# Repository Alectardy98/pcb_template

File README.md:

# PCB Template 
    A template pcb made on www.keebal.com

All Supported Layouts can be seen [here](http://www.keyboard-layout-editor.com/#/gists/8a30e97cff93e199c105295b596f17f3)

USB/QMK atmega32u4 pcb for The RAMA x ION Zenith

- The firmware can be found in the firmware folder
- All files for production though JLCPCB can be found in the JLCPCB folder
- This PCB supports an ATMEGA32u4-AU and works via qmk
- Layouts support both MX and alps Switches

Released without warranty, use at your own risk.  

---
| Authors | 

Alectardy98

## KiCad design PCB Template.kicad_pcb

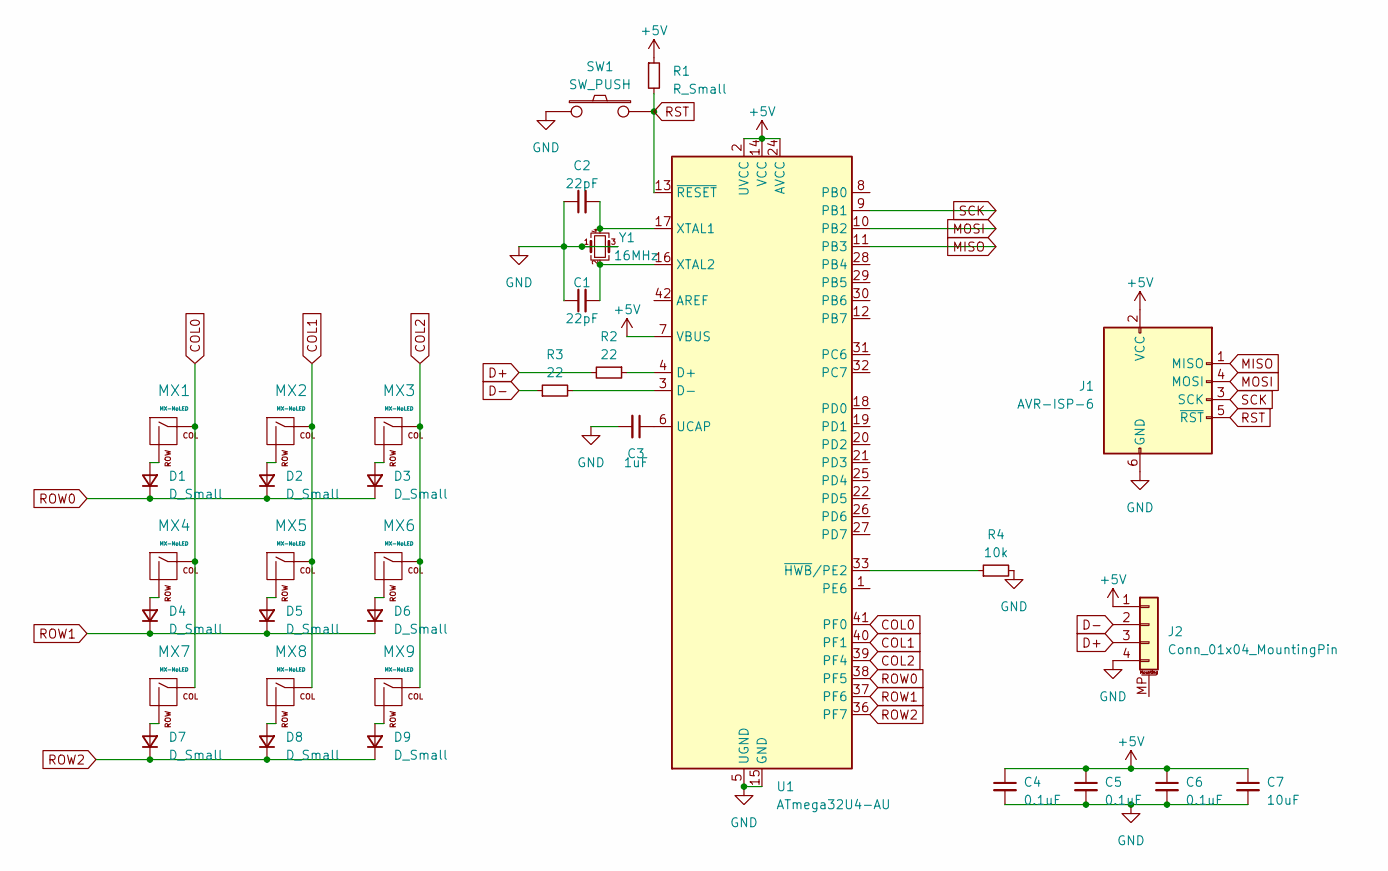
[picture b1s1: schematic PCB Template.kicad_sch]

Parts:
C1, C2: 22pF; C_0805_2012Metric
C3: 1uF; C_0805_2012Metric
C4, C5, C6: 0.1uF; C_0805_2012Metric
C7: 10uF; C_0805_2012Metric
D1, D2, D3, D4, D5, D6, D7, D8, D9: D_Small; D_SOD-123
J1: AVR-ISP-6; PinSocket_2x03_P2.54mm_Vertical
J2: Conn_01x04_MountingPin; JST_SH_SM04B-SRSS-TB_1x04-1MP_P1.00mm_Horizontal
MX1, MX2, MX3, MX4, MX5, MX6, MX7, MX8, MX9: MX-NoLED; MX-1U-NoLED
R1: R_Small
R2, R3: 22; R_0805_2012Metric
R4: 10k; R_0805_2012Metric
SW1: SW_PUSH
U1: ATmega32U4-AU; atmega32u4-mu-and-au
Y1: 16MHz; Crystal_SMD_3225-4Pin_3.2x2.5mm

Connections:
+5V: C4.1, C5.1, C6.1, C7.1, J1.2 (VCC), J2.1, R1.1, U1.2 (UVCC), U1.7 (VBUS), U1.14 (VCC), U1.24 (AVCC), U1.34 (VCC), U1.44 (AVCC)
COL0: MX1.1 (COL), MX4.1 (COL), MX7.1 (COL), U1.41 (PF0)
COL1: MX2.1 (COL), MX5.1 (COL), MX8.1 (COL), U1.40 (PF1)
COL2: MX3.1 (COL), MX6.1 (COL), MX9.1 (COL), U1.39 (PF4)
D+: J2.3, R2.2
D-: J2.2, R3.1
GND: C1.1, C2.1, C3.2, C4.2, C5.2, C6.2, C7.2, J1.6 (GND), J2.4, R4.2, SW1.1, U1.5 (UGND), U1.15 (GND), U1.23 (GND), U1.35 (GND), U1.43 (GND), U1.45, Y1.1, Y1.3
MISO: J1.1 (MISO), U1.11 (PB3)
MOSI: J1.4 (MOSI), U1.10 (PB2)
unnamed: D1.2 (A), MX1.2 (ROW)
unnamed: D2.2 (A), MX2.2 (ROW)
unnamed: D3.2 (A), MX3.2 (ROW)
unnamed: D4.2 (A), MX4.2 (ROW)
unnamed: D5.2 (A), MX5.2 (ROW)
unnamed: D6.2 (A), MX6.2 (ROW)
unnamed: D7.2 (A), MX7.2 (ROW)
unnamed: D8.2 (A), MX8.2 (ROW)
unnamed: D9.2 (A), MX9.2 (ROW)
unnamed: R2.1, U1.4 (D+)
unnamed: R3.2, U1.3 (D-)
unnamed: C3.1, U1.6 (UCAP)
unnamed: C2.2, U1.17 (XTAL1), Y1.4
unnamed: C1.2, U1.16 (XTAL2), Y1.2
unnamed: R4.1, U1.33 (~HWB/PE2)
ROW0: D1.1 (K), D2.1 (K), D3.1 (K), U1.38 (PF5)
ROW1: D4.1 (K), D5.1 (K), D6.1 (K), U1.37 (PF6)
ROW2: D7.1 (K), D8.1 (K), D9.1 (K), U1.36 (PF7)
RST: J1.5 (~RST), R1.2, SW1.2, U1.13 (~RESET)
SCK: J1.3 (SCK), U1.9 (PB1)

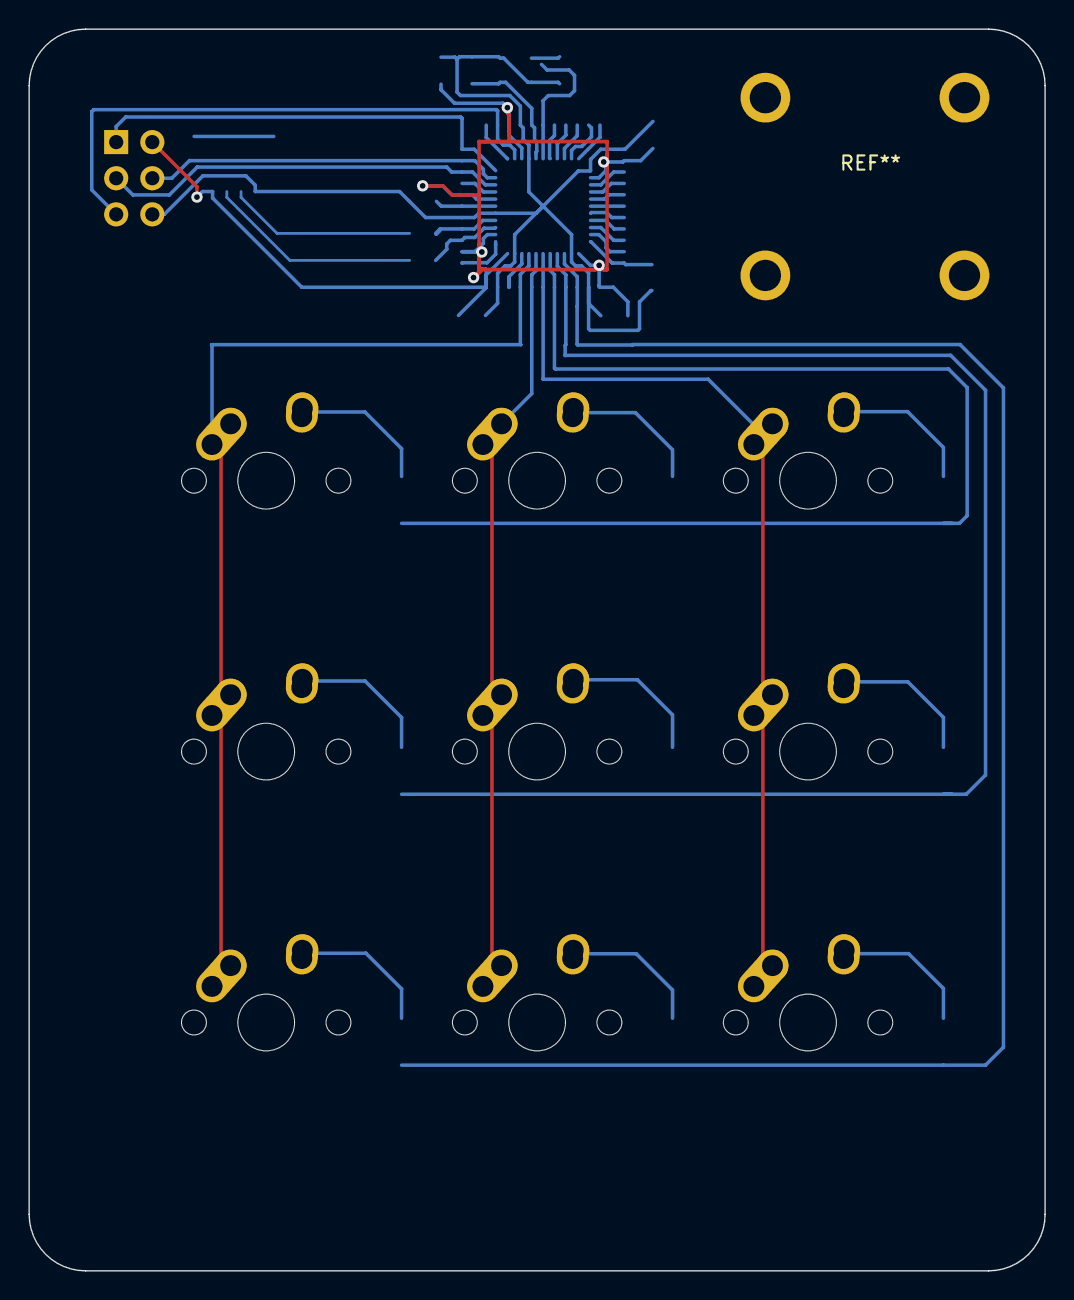
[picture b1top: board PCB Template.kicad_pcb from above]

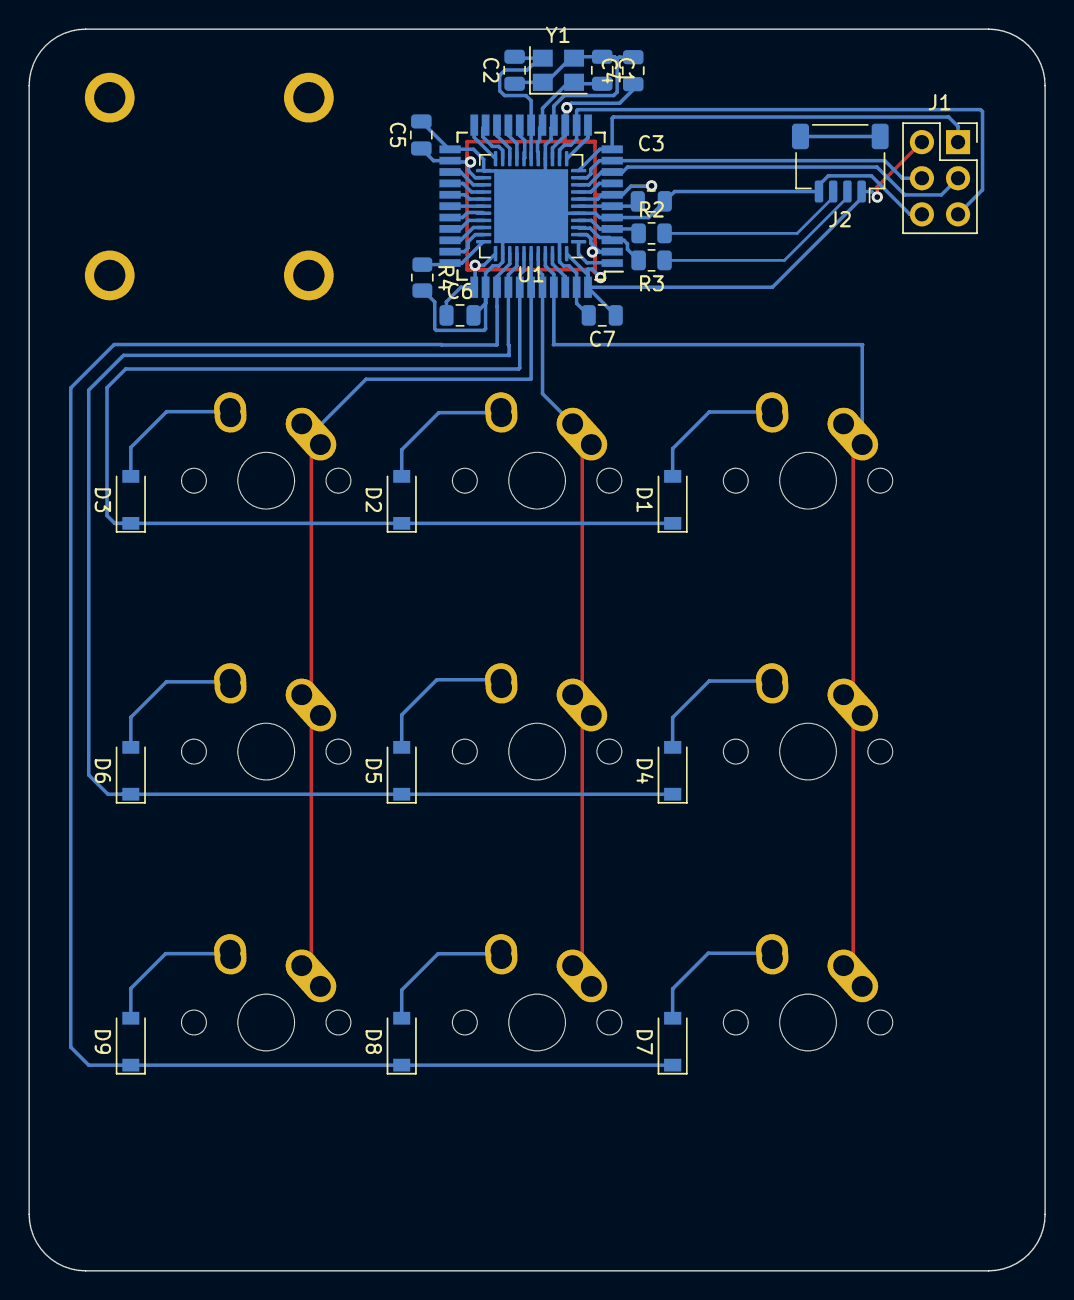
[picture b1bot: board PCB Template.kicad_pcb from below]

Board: 2 copper layers, 71.4 x 87.3 mm, 32 parts (23 on the bottom side), 29 nets.

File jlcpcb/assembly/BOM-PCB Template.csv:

Comment,Designator,Footprint,LCSC
ATmega32U4-AU,U1,atmega32u4-mu-and-au,C112161
Conn_01x04_MountingPin,J2,JST_SH_SM04B-SRSS-TB_1x04-1MP_P1.00mm_Horizontal,C160404
D_Small,"D1,D2,D3,D4,D5,D6,D7,D8,D9",D_SOD-123,C2099
MX-NoLED,MX4,MX-1U-NoLED,
MX-NoLED,MX9,MX-1U-NoLED,
MX-NoLED,MX7,MX-1U-NoLED,
MX-NoLED,MX5,MX-1U-NoLED,
MX-NoLED,MX6,MX-1U-NoLED,
MX-NoLED,MX8,MX-1U-NoLED,
MX-NoLED,MX1,MX-1U-NoLED,
MX-NoLED,MX3,MX-1U-NoLED,
MX-NoLED,MX2,MX-1U-NoLED,
1uF,C3,C_0805_2012Metric,
22pF,C2,C_0805_2012Metric,
10uF,C7,C_0805_2012Metric,
22pF,C1,C_0805_2012Metric,
0.1uF,C6,C_0805_2012Metric,
22,R3,R_0805_2012Metric,
22,R2,R_0805_2012Metric,
AVR-ISP-6,J1,PinSocket_2x03_P2.54mm_Vertical,
10k,R4,R_0805_2012Metric,
0.1uF,C5,C_0805_2012Metric,
16MHz,Y1,Crystal_SMD_3225-4Pin_3.2x2.5mm,
0.1uF,C4,C_0805_2012Metric,

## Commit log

2022-10-19 push
2022-10-19 add meta
2022-10-20 Push Changes for 32u4
2022-10-20 Push Fab Files
2022-10-21 Changes to the MU/AU
